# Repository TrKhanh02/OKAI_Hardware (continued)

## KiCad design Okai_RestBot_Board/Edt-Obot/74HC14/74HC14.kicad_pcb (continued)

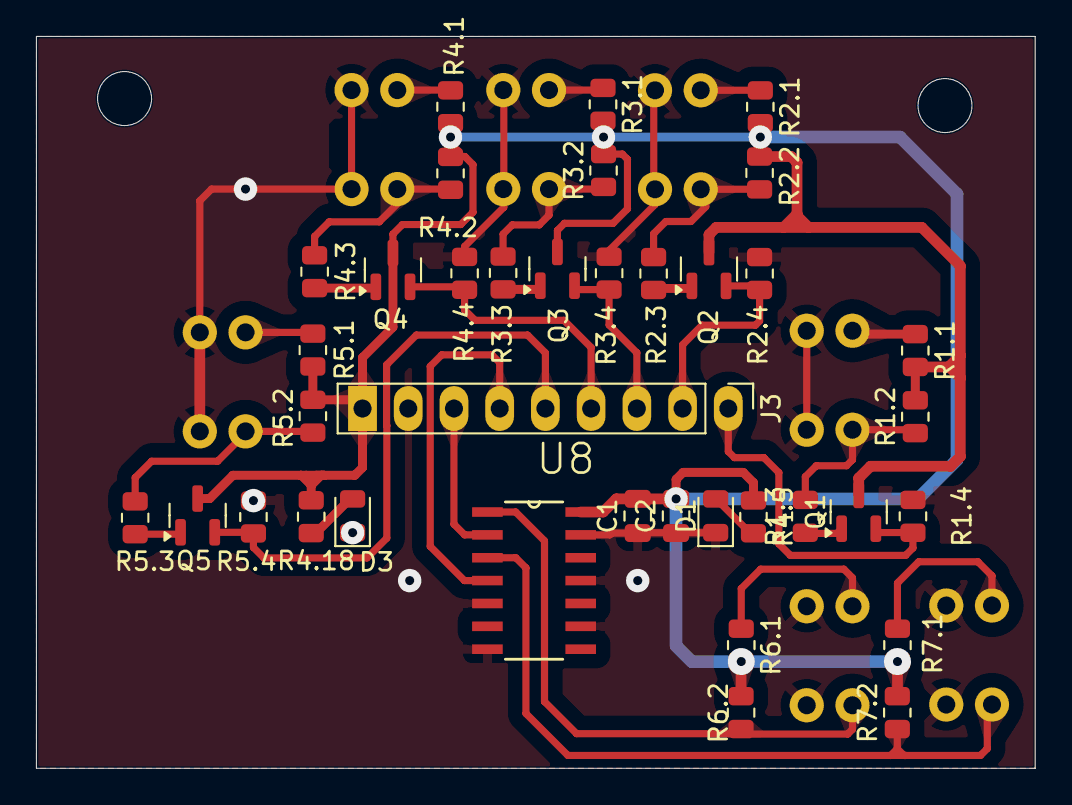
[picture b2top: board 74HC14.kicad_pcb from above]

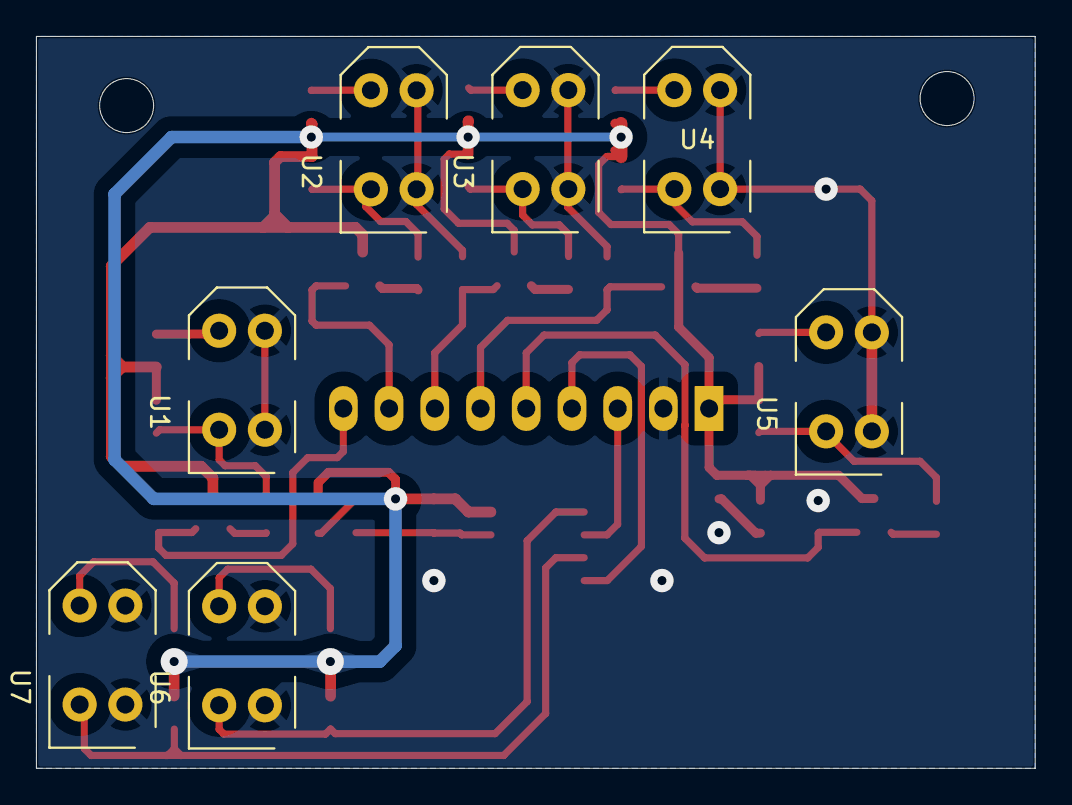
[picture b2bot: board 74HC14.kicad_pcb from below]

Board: 2 copper layers, 55.5 x 40.7 mm, 44 parts (7 on the bottom side), 30 nets.

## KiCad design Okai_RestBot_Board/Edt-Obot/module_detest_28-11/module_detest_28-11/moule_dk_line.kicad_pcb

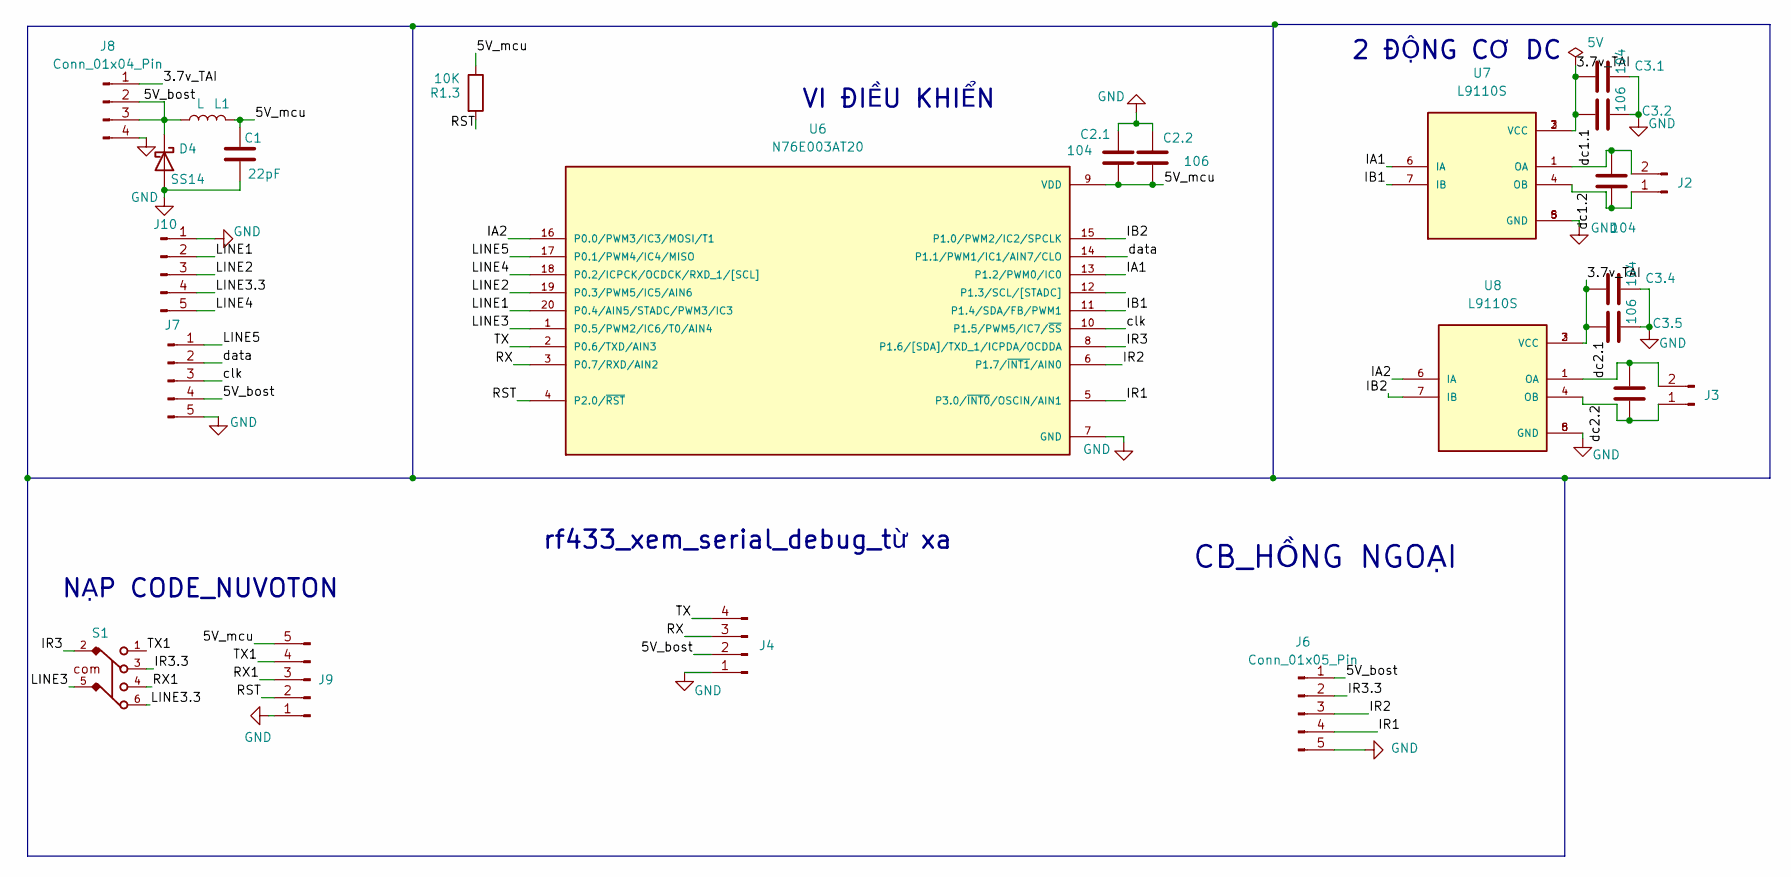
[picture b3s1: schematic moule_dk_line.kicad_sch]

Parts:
C1: 22pF; C_1206_3216Metric
C2.1, C3.1, C3.3, C3.4, C3.6: 104; C_0805_2012Metric
C2.2, C3.2, C3.5: 106; C_0805_2012Metric
D4: SS14; D_SMA
J2, J3: Conn_01x02_Pin; PinHeader_1x02_P2.54mm_Vertical
J4, J8: Conn_01x04_Pin; PinHeader_1x04_P2.54mm_Vertical
J6, J7, J9, J10: Conn_01x05_Pin; PinHeader_1x05_P2.54mm_Vertical
L1: L; L_6.3x6.3_H3
R1.3: 10K; R_0805_2012Metric
S1: 452406020024
U6: N76E003AT20; SOP65P640X120-20N; PARTREV 1.04
U7, U8: L9110S; SOIC127P599X172-8N; PARTREV NA

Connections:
/3.7v_TAI: C3.1.1, C3.2.1, C3.4.1, C3.5.1, J8.1, U7.2 (VCC), U7.3 (VCC), U8.2 (VCC), U8.3 (VCC)
/5V_bost: D4.1 (K), J4.2, J6.1, J7.4, J8.2, J8.3, L1.1
/5V_mcu: C1.1, C2.1.1, C2.2.1, J9.5, L1.2, R1.3.1, U6.9 (VDD)
/IA1: U6.13 (P1.2/PWM0/IC0), U7.6 (IA)
/IA2: U6.16 (P0.0/PWM3/IC3/MOSI/T1), U8.6 (IA)
/IB1: U6.11 (P1.4/SDA/FB/PWM1), U7.7 (IB)
/IB2: U6.15 (P1.0/PWM2/IC2/SPCLK), U8.7 (IB)
/IR1: J6.4, U6.5 (P3.0/~INT0/OSCIN/AIN1)
/IR2: J6.3, U6.6 (P1.7/~INT1/AIN0)
/IR3: S1.2, U6.8 (P1.6/[SDA]/TXD_1/ICPDA/OCDDA)
/IR3.3: J6.2, S1.3
/LINE1: J10.2, U6.20 (P0.4/AIN5/STADC/PWM3/IC3)
/LINE2: J10.3, U6.19 (P0.3/PWM5/IC5/AIN6)
/LINE3: S1.5, U6.1 (P0.5/PWM2/IC6/T0/AIN4)
/LINE3.3: J10.4, S1.6
/LINE4: J10.5, U6.18 (P0.2/ICPCK/OCDCK/RXD_1/[SCL])
/LINE5: J7.1, U6.17 (P0.1/PWM4/IC4/MISO)
/RST: J9.2, R1.3.2, U6.4 (P2.0/~RST)
/RX: J4.3, U6.3 (P0.7/RXD/AIN2)
/RX1: J9.3, S1.4
/TX: J4.4, U6.2 (P0.6/TXD/AIN3)
/TX1: J9.4, S1.1
/clk: J7.3, U6.10 (P1.5/PWM5/IC7/~SS)
/data: J7.2, U6.14 (P1.1/PWM1/IC1/AIN7/CLO)
/dc1.1: C3.3.1, J2.2, U7.1 (OA)
/dc1.2: C3.3.2, J2.1, U7.4 (OB)
/dc2.1: C3.6.1, J3.2, U8.1 (OA)
/dc2.2: C3.6.2, J3.1, U8.4 (OB)
GND: C1.2, C2.1.2, C2.2.2, C3.1.2, C3.2.2, C3.4.2, C3.5.2, D4.2 (A), J4.1, J6.5, J7.5, J8.4, J9.1, J10.1, U6.7 (GND), U7.5 (GND), U7.8 (GND), U8.5 (GND), U8.8 (GND)

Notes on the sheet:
VI ĐIỀU KHIỂN
CB_HỒNG NGOẠI
NẠP CODE_NUVOTON
2 ĐỘNG CƠ DC
rf433_xem_serial_debug_từ xa

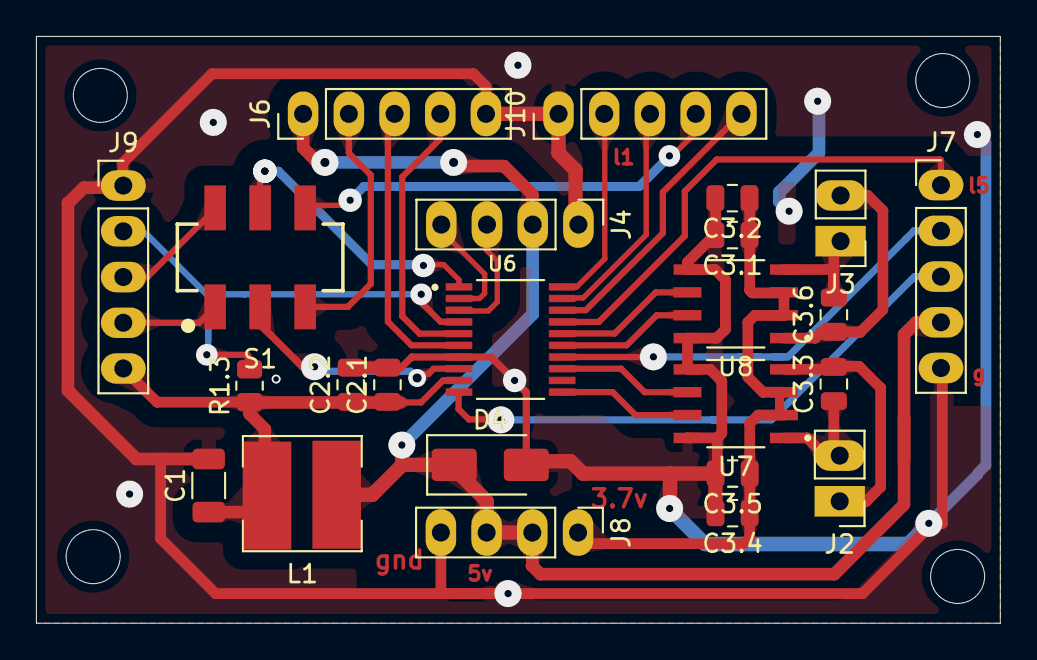
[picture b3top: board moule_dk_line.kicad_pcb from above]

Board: 2 copper layers, 53.5 x 32.6 mm, 24 parts (0 on the bottom side), 29 nets.

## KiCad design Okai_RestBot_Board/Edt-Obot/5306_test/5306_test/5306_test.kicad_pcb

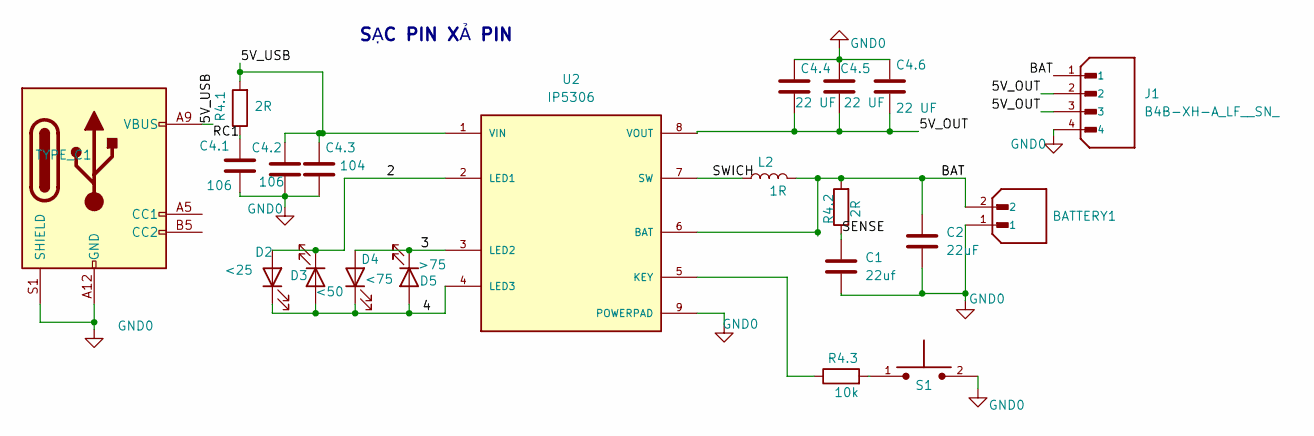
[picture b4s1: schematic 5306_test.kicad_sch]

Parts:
BATTERY1: B2B-XH-A_LF__SN_; JST_B2B-XH-A_LF__SN_; PARTREV N/A
C1: 22uf; C_1206_3216Metric_Pad1.33x1.80mm_HandSolder
C2: 22uF; C_1206_3216Metric_Pad1.33x1.80mm_HandSolder
C4.1, C4.2: 106; C_1206_3216Metric_Pad1.33x1.80mm_HandSolder
C4.3: 104; C_0805_2012Metric
C4.4, C4.5, C4.6: 22 UF; C_1206_3216Metric_Pad1.33x1.80mm_HandSolder
D2: <25; LED_0805_2012Metric_Pad1.15x1.40mm_HandSolder
D3: <50; LED_0805_2012Metric_Pad1.15x1.40mm_HandSolder
D4: <75; LED_0805_2012Metric_Pad1.15x1.40mm_HandSolder
D5: >75; LED_0805_2012Metric_Pad1.15x1.40mm_HandSolder
J1: B4B-XH-A_LF__SN_; JST_B4B-XH-A_LF__SN_; PARTREV 7/4/21
L2: 1R; L_7.3x7.3_H4.5
R4.1, R4.2: 2R; R_0805_2012Metric
R4.3: 10k; R_0805_2012Metric_Pad1.20x1.40mm_HandSolder
S1: TS10-63-26-BE-250-SMT-TR; SW_TS10-63-26-BE-250-SMT-TR; PARTREV 1.0
TYPE_C1: USB_C_Receptacle_PowerOnly_6P; USB_C_Receptacle_GCT_USB4125-xx-x_6P_TopMnt_Horizontal
U2: IP5306; SOP127P600X165-9N; PARTREV 1.31

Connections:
/2: D2.2 (A), D3.1 (K), U2.2 (LED1)
/3: D4.2 (A), D5.1 (K), U2.3 (LED2)
/4: D2.1 (K), D3.2 (A), D4.1 (K), D5.2 (A), U2.4 (LED3)
/5V_OUT: C4.4.2, C4.5.2, C4.6.2, J1.2, J1.3, U2.8 (VOUT)
/5V_USB: C4.2.1, C4.3.1, R4.1.2, TYPE_C1.A9 (VBUS), TYPE_C1.B9 (VBUS), U2.1 (VIN)
/BAT: BATTERY1.2, C2.1, J1.1, L2.2, R4.2.2, U2.6 (BAT)
/RC1: C4.1.1, R4.1.1
/SENSE: C1.1, R4.2.1
/SWICH: L2.1, U2.7 (SW)
GND0: BATTERY1.1, C1.2, C2.2, C4.1.2, C4.2.2, C4.3.2, C4.4.1, C4.5.1, C4.6.1, J1.4, S1.2, TYPE_C1.A12 (GND), TYPE_C1.B12 (GND), TYPE_C1.S1 (SHIELD), U2.9 (POWERPAD)
unnamed: R4.3.2, S1.1
unnamed: R4.3.1, U2.5 (KEY)

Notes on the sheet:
SẠC PIN XẢ PIN

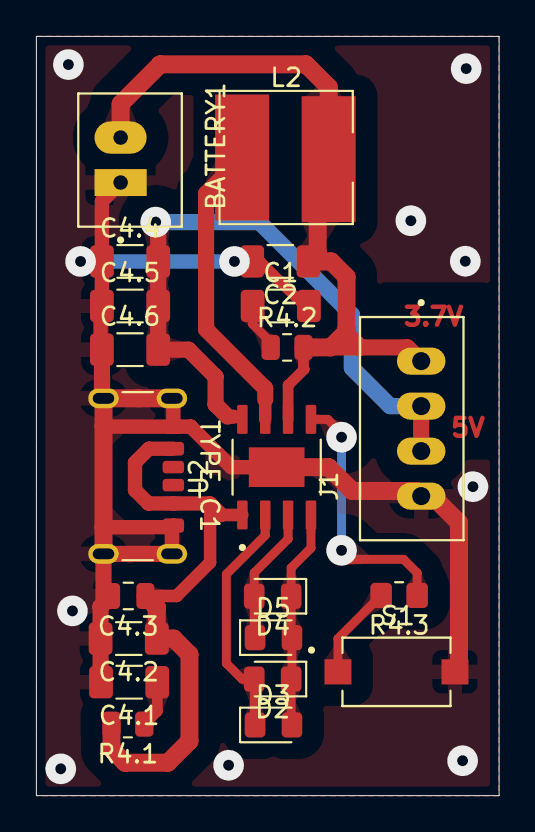
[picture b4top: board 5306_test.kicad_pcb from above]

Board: 2 copper layers, 25.7 x 42.2 mm, 21 parts (0 on the bottom side), 12 nets.

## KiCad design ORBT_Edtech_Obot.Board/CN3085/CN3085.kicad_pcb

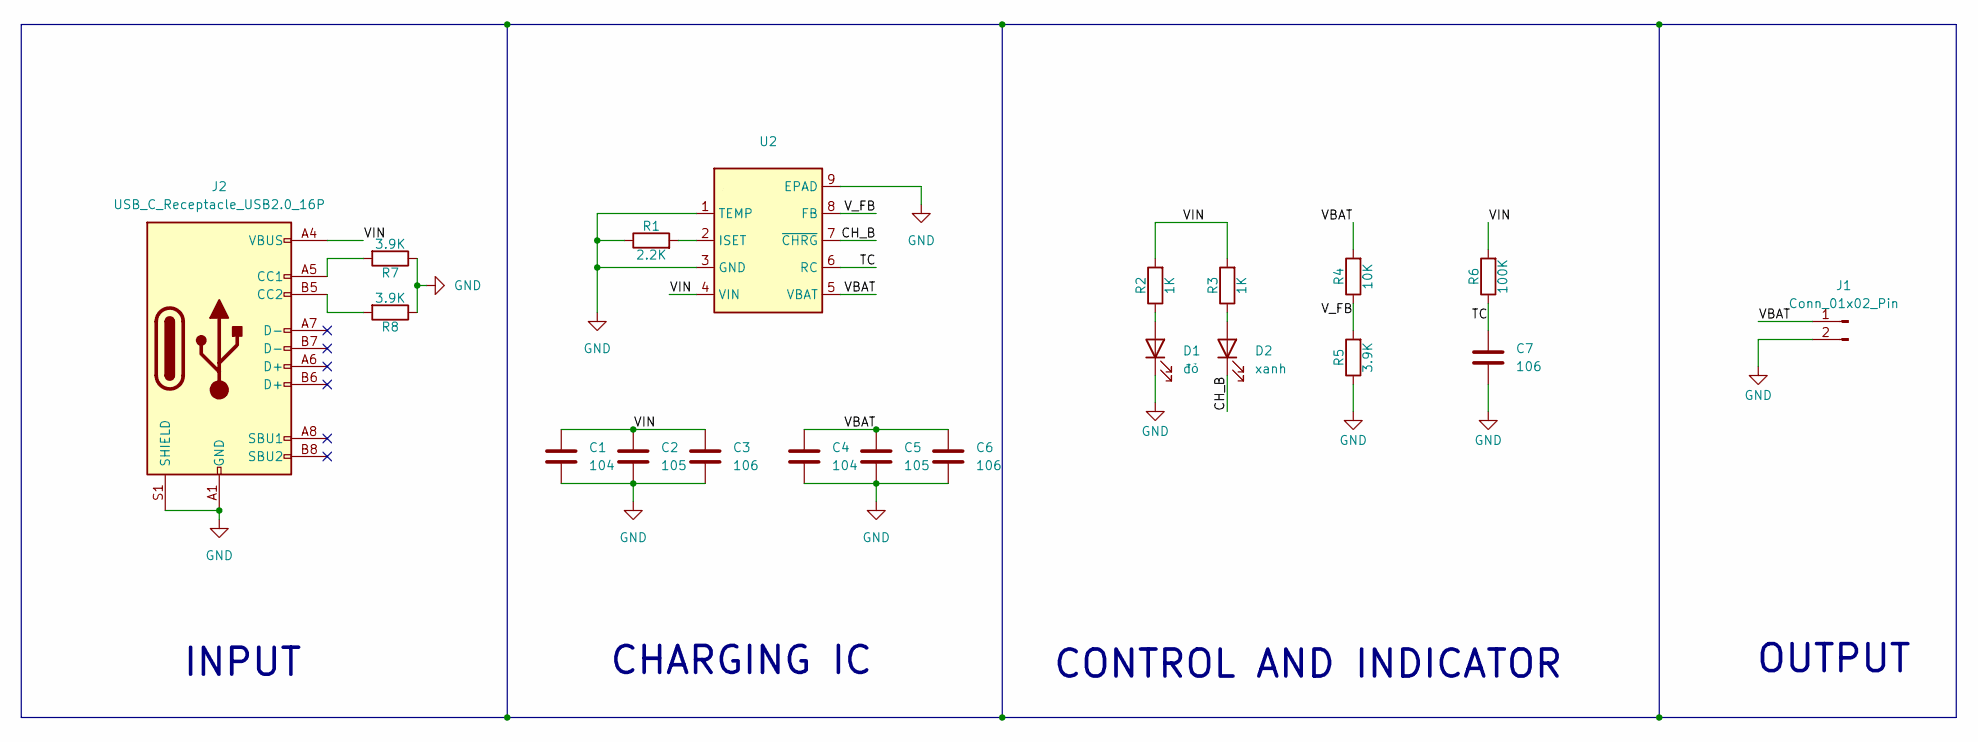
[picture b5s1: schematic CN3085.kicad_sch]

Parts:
C1, C4: 104; C_0805_2012Metric
C2, C5: 105; C_0805_2012Metric
C3, C6, C7: 106; C_0805_2012Metric
D1: đỏ; LED_0805_2012Metric_Pad1.15x1.40mm_HandSolder
D2: xanh; LED_0805_2012Metric_Pad1.15x1.40mm_HandSolder
J1: Conn_01x02_Pin; PinHeader_1x02_P2.54mm_Vertical
J2: USB_C_Receptacle_USB2.0_16P; USB_C_Receptacle_GCT_USB4105-xx-A_16P_TopMnt_Horizontal
R1: 2.2K; R_0805_2012Metric_Pad1.20x1.40mm_HandSolder
R2, R3: 1K; R_0805_2012Metric_Pad1.20x1.40mm_HandSolder
R4: 10K; R_0805_2012Metric_Pad1.20x1.40mm_HandSolder
R5, R7, R8: 3.9K; R_0805_2012Metric_Pad1.20x1.40mm_HandSolder
R6: 100K; R_0805_2012Metric_Pad1.20x1.40mm_HandSolder
U2: CN3085

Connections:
/CH_B: D2.1 (K), U2.7 (~CHRG)
/TC: C7.2, R6.1, U2.6 (RC)
/VBAT: C4.2, C5.2, C6.2, J1.1, R4.2, U2.5 (VBAT)
/VIN: C1.2, C2.2, C3.2, J2.A4 (VBUS), J2.A9 (VBUS), J2.B4 (VBUS), J2.B9 (VBUS), R2.2, R3.2, R6.2, U2.4 (VIN)
/V_FB: R4.1, R5.2, U2.8 (FB)
GND: C1.1, C2.1, C3.1, C4.1, C5.1, C6.1, C7.1, D1.1 (K), J1.2, J2.A1 (GND), J2.A12 (GND), J2.B1 (GND), J2.B12 (GND), J2.S1 (SHIELD), R1.1, R5.1, R7.1, R8.1, U2.1 (TEMP), U2.3 (GND), U2.9 (EPAD)
unnamed: D1.2 (A), R2.1
unnamed: D2.2 (A), R3.1
unnamed: J2.A5 (CC1), R7.2
unnamed: J2.B5 (CC2), R8.2
unnamed: R1.2, U2.2 (ISET)

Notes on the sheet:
CHARGING IC
INPUT
OUTPUT
CONTROL AND INDICATOR

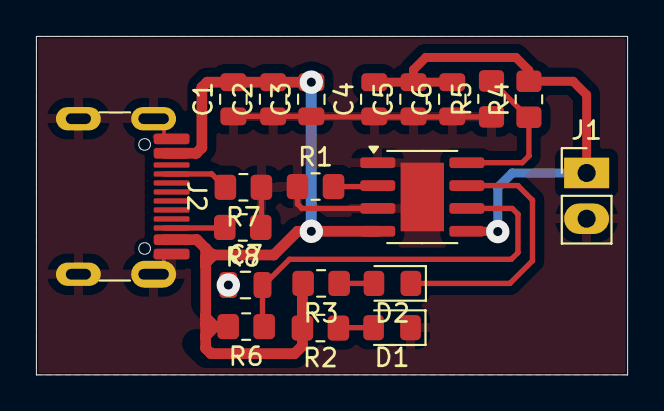
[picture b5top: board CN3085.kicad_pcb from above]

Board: 2 copper layers, 32.8 x 18.8 mm, 20 parts (0 on the bottom side), 11 nets.

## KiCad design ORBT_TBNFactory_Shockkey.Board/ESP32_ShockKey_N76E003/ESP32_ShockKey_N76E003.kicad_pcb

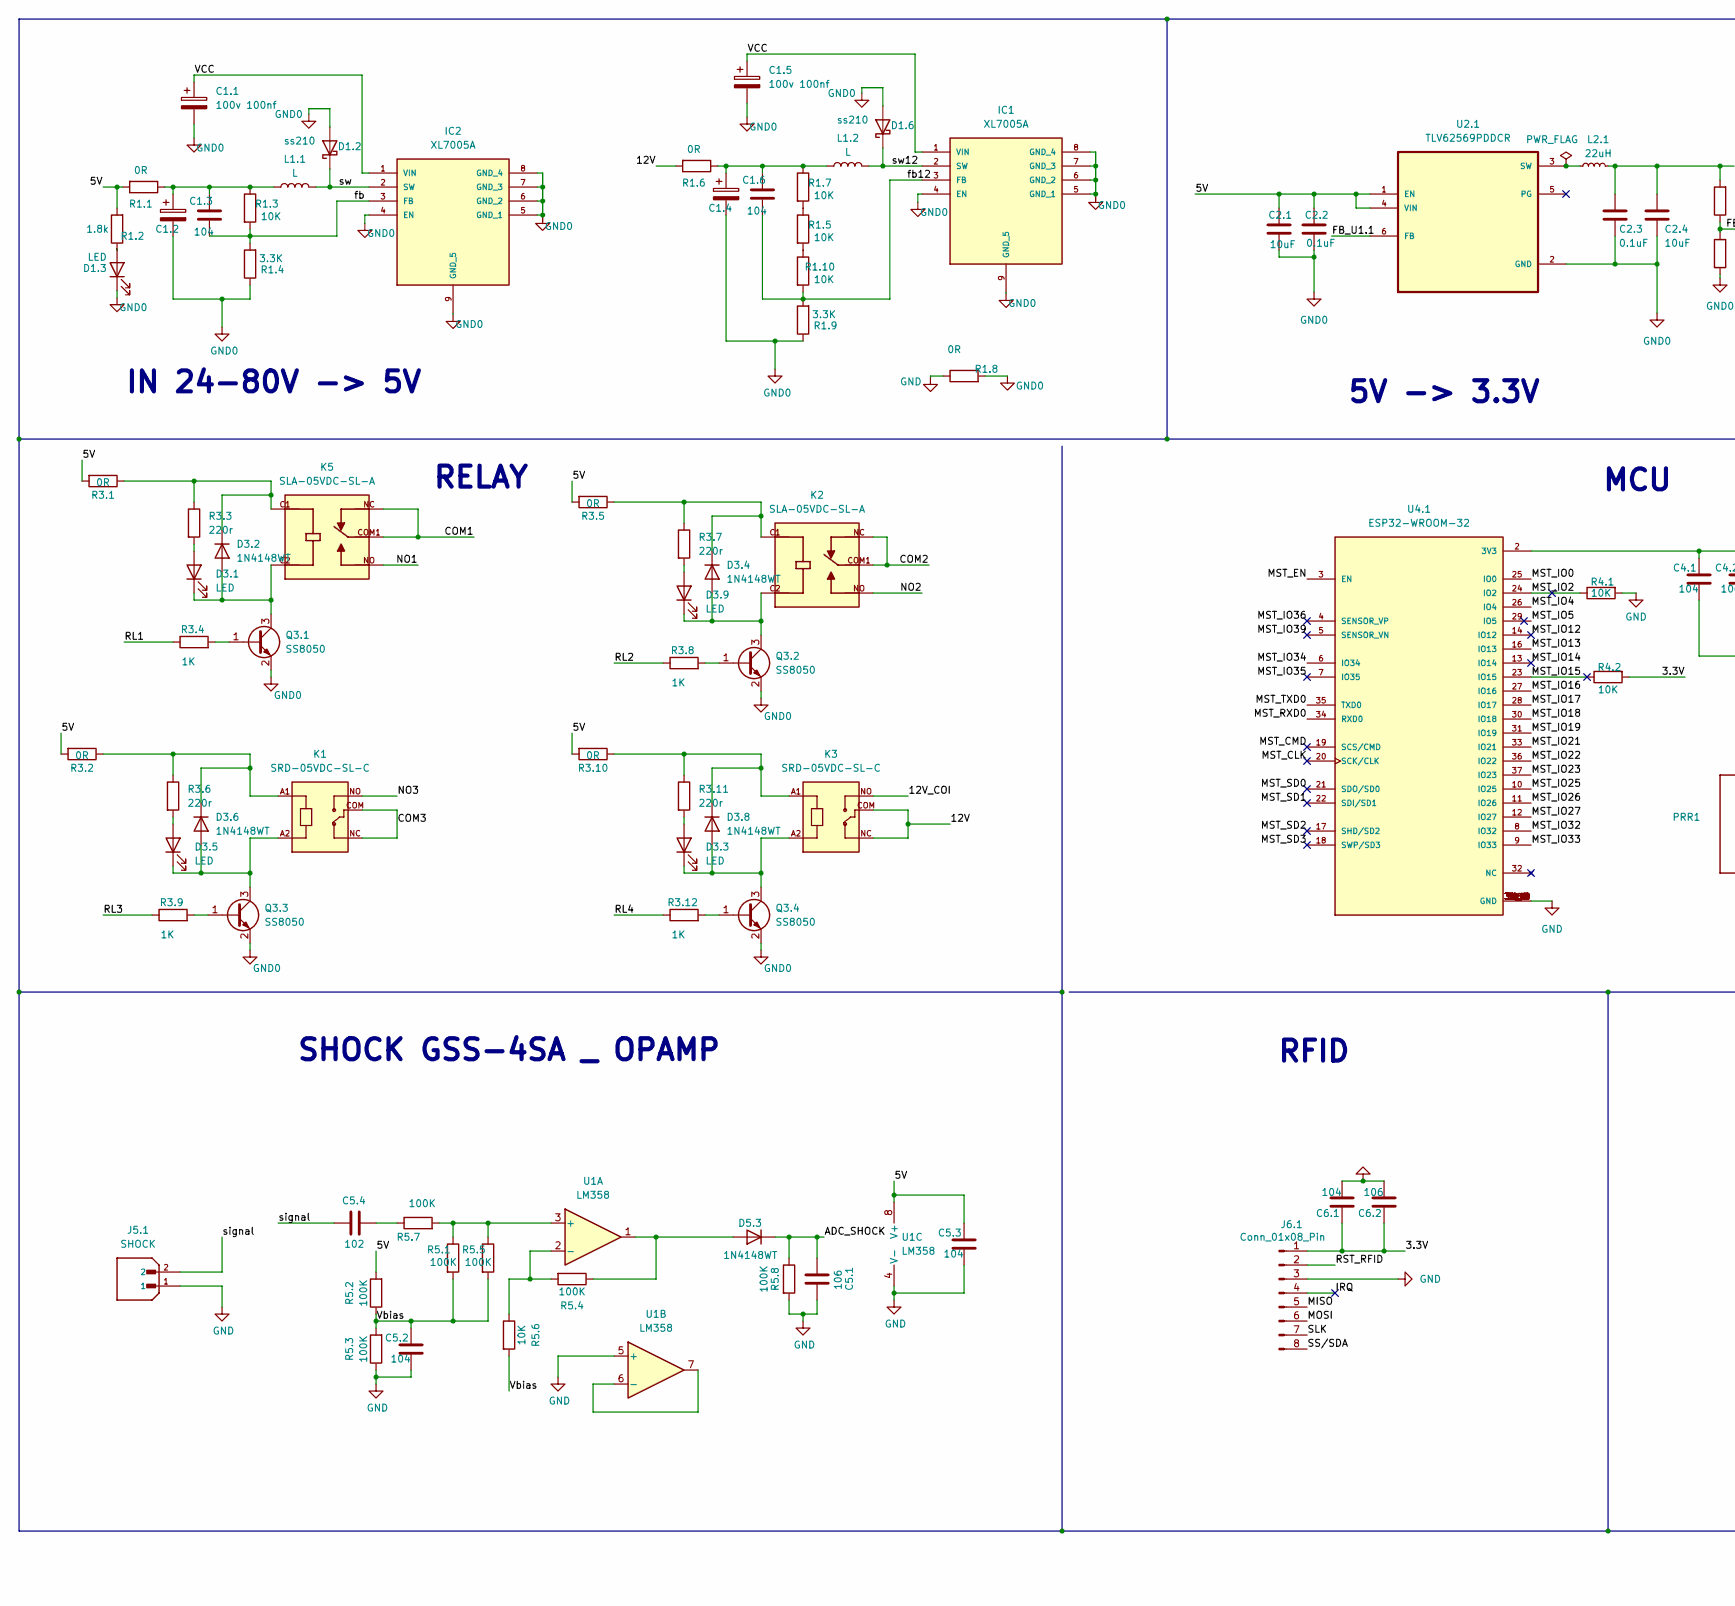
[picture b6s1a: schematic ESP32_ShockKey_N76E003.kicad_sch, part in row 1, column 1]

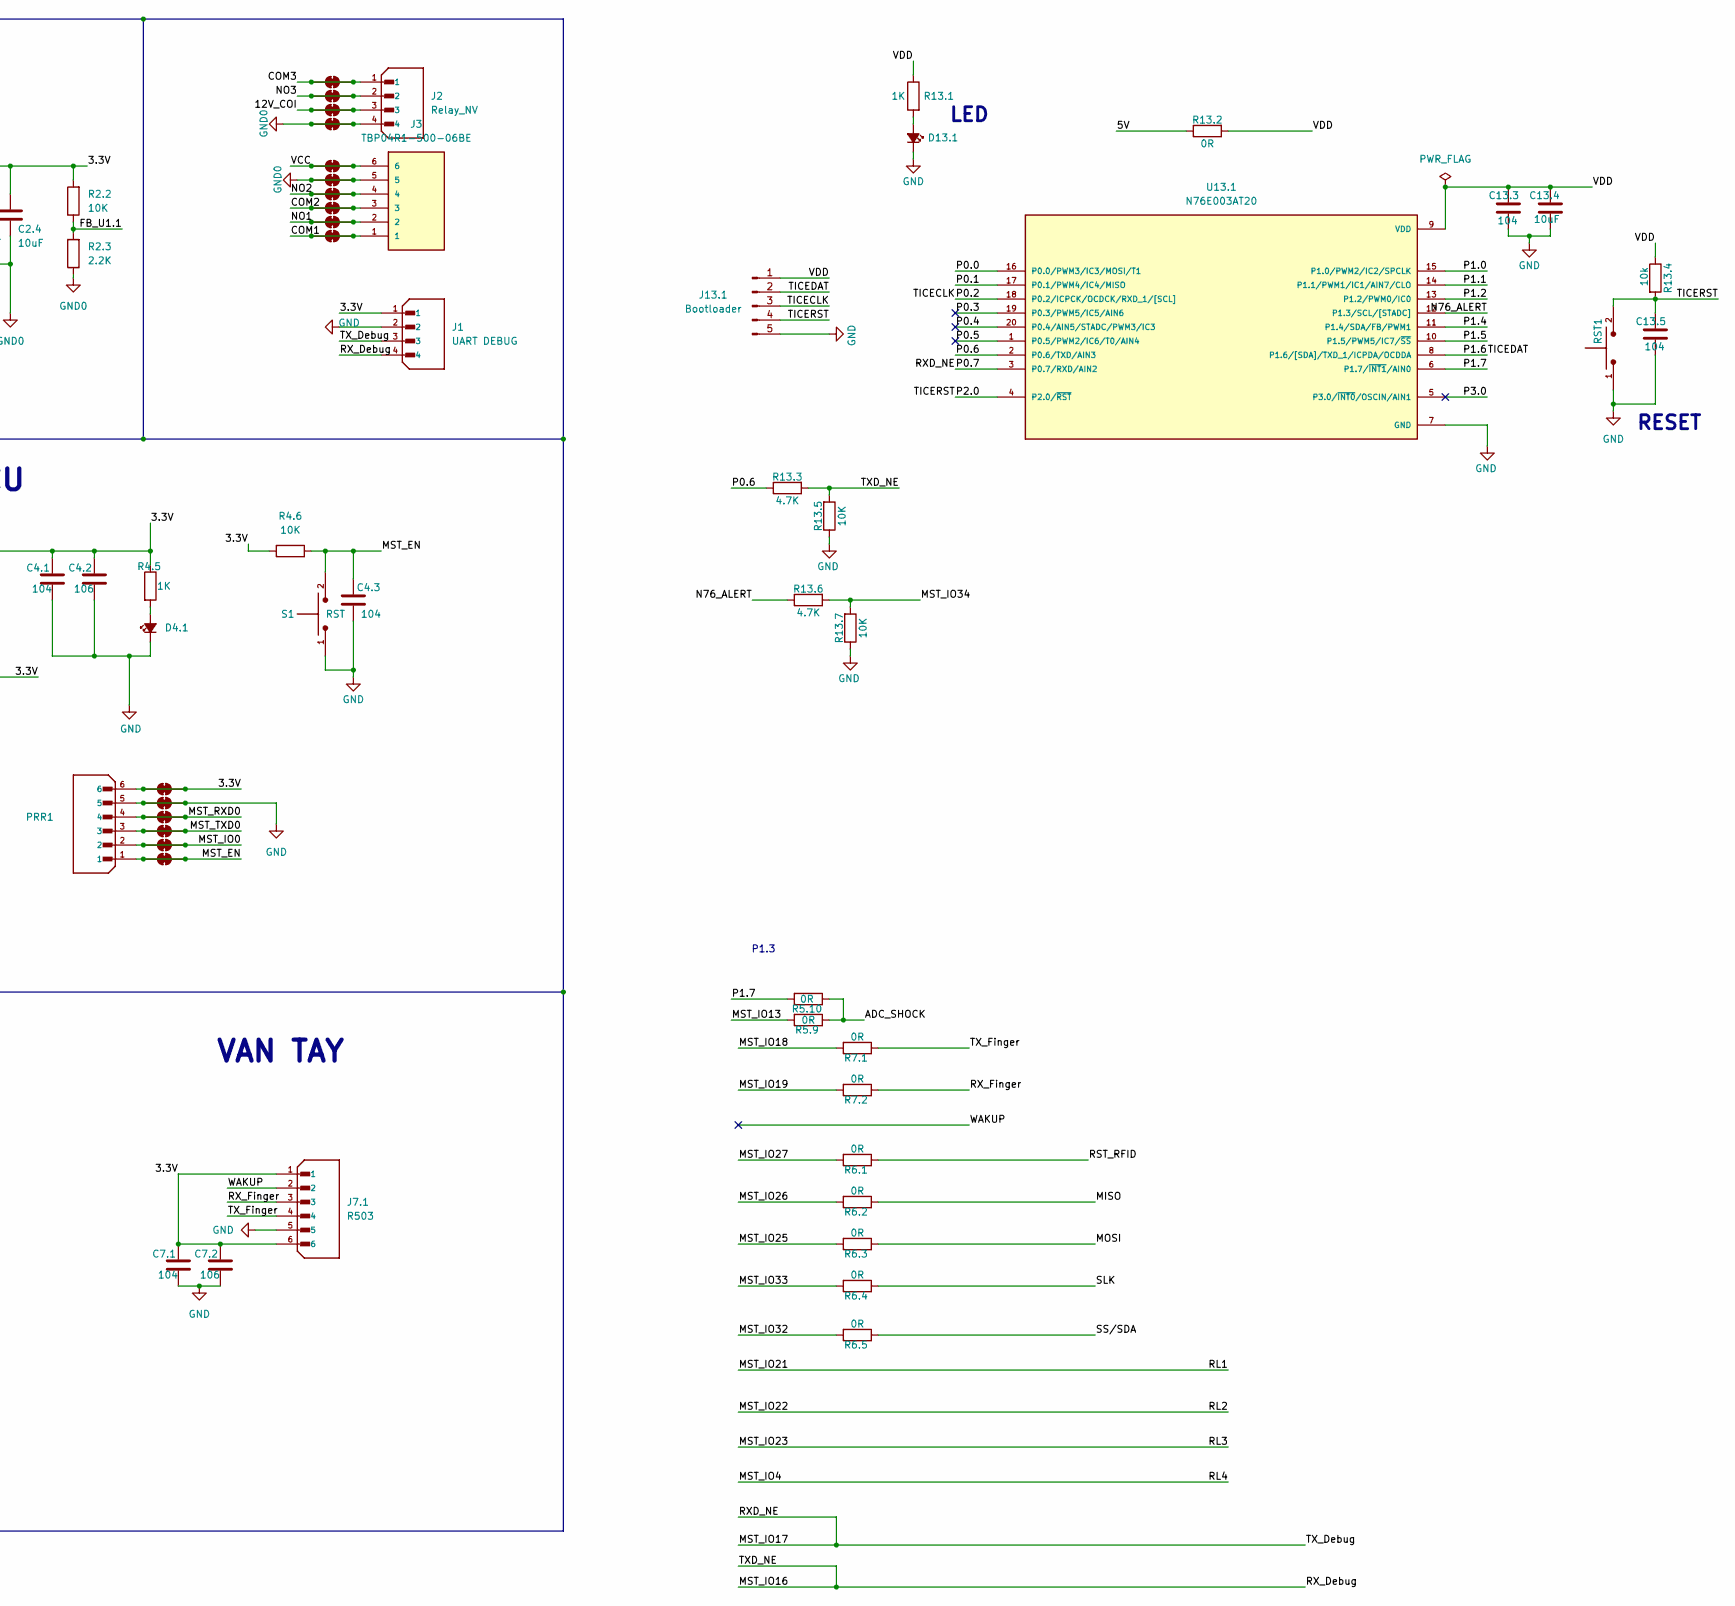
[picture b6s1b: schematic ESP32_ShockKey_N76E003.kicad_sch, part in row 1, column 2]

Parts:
C1.1, C1.5: 100v 100nf; CP_Radial_D6.3mm_P2.50mm
C1.2, C1.4: C_Polarized; CP_Elec_6.3x5.4
C1.3, C1.6, C4.3: 104; C_0805_2012Metric
C2.1, C2.4: 10uF; C_0805_2012Metric
C2.2, C2.3: 0.1uF; C_0805_2012Metric
C4.1, C5.2, C5.3, C6.1, C7.1, C13.3, C13.5: 104; C_0805_2012Metric_Pad1.18x1.45mm_HandSolder
C4.2, C5.1, C6.2, C7.2: 106; C_0805_2012Metric_Pad1.18x1.45mm_HandSolder
C5.4: 102; C_0805_2012Metric_Pad1.18x1.45mm_HandSolder
C13.4: 10uF; C_0805_2012Metric_Pad1.18x1.45mm_HandSolder
D1.2, D1.6: ss210; D_SMA
D1.3, D3.1, D3.3, D3.5, D3.9: LED; LED_0805_2012Metric
D3.2, D3.4, D3.6, D3.8, D5.3: 1N4148WT; D_SOD-523
D4.1, D13.1: LED_Small_Filled; LED_0805_2012Metric_Pad1.15x1.40mm_HandSolder
IC1, IC2: XL7005A; SOIC127P600X175-9N; Manufacturer_Part_Number XL7005A
J1: UART DEBUG; JST_B4B-XH-A_LF__SN_; PARTREV 7/4/21
J2: Relay_NV; JST_B4B-XH-A_LF__SN_; PARTREV 7/4/21
J3: TBP04R1-500-06BE; CUI_TBP04R1-500-06BE; PARTREV 1.0
J5.1: SHOCK; JST_B2B-XH-A_LF__SN_; PARTREV N/A
J6.1: Conn_01x08_Pin; PinHeader_1x08_P2.54mm_Vertical
J7.1: R503; JST_B6B-XH-A_LF__SN_; PARTREV 7/4/21
J13.1: Bootloader; PinHeader_1x05_P2.54mm_Vertical
JP1, JP2, JP3, JP4, JP5, JP6, JP7, JP8, JP9, JP10, JP11, JP12, JP13, JP14, JP15, JP16: SolderJumper_2_Bridged; SolderJumper-2_P1.3mm_Bridged_Pad1.0x1.5mm
K1, K3: SRD-05VDC-SL-C; RELAY_SRD-05VDC-SL-C
K2, K5: SLA-05VDC-SL-A; RELAY_SLA-12VDC-SL-C
L1.1, L1.2: L; L_10.4x10.4_H4.8
L2.1: 22uH; L_Ferrocore_DLG-0705
PRR1: B6B-XH-A_LF__SN_; JST_B6B-XH-A_LF__SN_; PARTREV 7/4/21
Q3.1, Q3.2, Q3.3, Q3.4: SS8050; SOT-23
R1.1, R1.6, R1.8, R5.9, R5.10, R6.1, R6.2, R6.3, R6.4, R6.5, R7.1, R7.2: 0R; R_0805_2012Metric
R1.2: 1.8k; R_0805_2012Metric
R1.3, R1.5, R1.7, R1.10, R2.2, R4.6, R5.6: 10K; R_0805_2012Metric
R1.4, R1.9: 3.3K; R_0805_2012Metric
R2.3: 2.2K; R_0805_2012Metric
R3.1, R3.2, R3.5, R3.10, R13.2: 0R; R_0805_2012Metric_Pad1.20x1.40mm_HandSolder
R3.3, R3.6, R3.7, R3.11: 220r; R_0805_2012Metric_Pad1.20x1.40mm_HandSolder
R3.4, R3.8, R3.9, R3.12, R4.5, R13.1: 1K; R_0805_2012Metric_Pad1.20x1.40mm_HandSolder
R4.1, R4.2, R13.5, R13.7: 10K; R_0805_2012Metric_Pad1.20x1.40mm_HandSolder
R5.1, R5.2, R5.3, R5.4, R5.5, R5.7, R5.8: 100K; R_0805_2012Metric
R13.3, R13.6: 4.7K; R_0805_2012Metric_Pad1.20x1.40mm_HandSolder
R13.4: 10k; R_0805_2012Metric_Pad1.20x1.40mm_HandSolder
RST1: TS10-63-26-BE-250-SMT-TR; SW_TS10-63-26-BE-250-SMT-TR; PARTREV 1.0
S1: RST; SW_TS10-63-26-BE-250-SMT-TR; PARTREV 1.0
U1: LM358; LFCSP-8_2x2mm_P0.5mm
U2.1: TLV62569PDDCR; SOT95P280X110-6N
U4.1: ESP32-WROOM-32; MODULE_ESP32-WROOM-32
U13.1: N76E003AT20; SOP65P640X120-20N; PARTREV 1.04

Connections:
/3.3V: C2.3.1, C2.4.1, C4.1.1, C4.2.1, C6.1.1, C6.2.1, C7.1.1, C7.2.1, J1.1, J6.1.1, J7.1.1, J7.1.6, JP13.1 (A), JP13.2 (B), L2.1.1, PRR1.6, R2.2.2, R4.2.2, R4.5.1, R4.6.1, U4.1.2 (3V3)
/5V: C2.1.1, C2.2.1, C5.3.1, R1.1.2, R1.2.2, R3.1.2, R3.2.2, R3.5.2, R3.10.2, R5.2.2, R13.2.1, U1.8 (V+), U2.1.1 (EN), U2.1.4 (VIN)
/12V: K3.COM, K3.NC, R1.6.2
/12V_COI: J2.3, JP3.1 (A), JP3.2 (B), K3.NO
/ADC_SHOCK: C5.1.2, D5.3.1 (K), R5.8.1, R5.9.1, R5.10.1
/COM1: J3.1, JP16.1 (A), JP16.2 (B), K5.COM1, K5.COM2, K5.NC
/COM2: J3.3, JP14.1 (A), JP14.2 (B), K2.COM1, K2.COM2, K2.NC
/COM3: J2.1, JP1.1 (A), JP1.2 (B), K1.COM, K1.NC
/FB_U1.1: R2.2.1, R2.3.2, U2.1.6 (FB)
/IRQ: J6.1.4
/MISO: J6.1.5, R6.2.1
/MOSI: J6.1.6, R6.3.1
/MST_CLK: U4.1.20 (SCK/CLK)
/MST_CMD: U4.1.19 (SCS/CMD)
/MST_EN: C4.3.1, JP8.1 (A), JP8.2 (B), PRR1.1, R4.6.2, S1.2, U4.1.3 (EN)
/MST_IO0: JP9.1 (A), JP9.2 (B), PRR1.2, U4.1.25 (IO0)
/MST_IO2: R4.1.1, U4.1.24 (IO2)
/MST_IO4: R3.12.1, U4.1.26 (IO4)
/MST_IO5: U4.1.29 (IO5)
/MST_IO12: U4.1.14 (IO12)
/MST_IO13: R5.9.2, U4.1.16 (IO13)
/MST_IO14: U4.1.13 (IO14)
/MST_IO15: R4.2.1, U4.1.23 (IO15)
/MST_IO16: J1.4, R13.3.2, R13.5.2, U4.1.27 (IO16)
/MST_IO17: J1.3, U4.1.28 (IO17), U13.1.3 (P0.7/RXD/AIN2)
/MST_IO18: R7.1.2, U4.1.30 (IO18)
/MST_IO19: R7.2.2, U4.1.31 (IO19)
/MST_IO21: R3.4.1, U4.1.33 (IO21)
/MST_IO22: R3.8.1, U4.1.36 (IO22)
/MST_IO23: R3.9.1, U4.1.37 (IO23)
/MST_IO25: R6.3.2, U4.1.10 (IO25)
/MST_IO26: R6.2.2, U4.1.11 (IO26)
/MST_IO27: R6.1.2, U4.1.12 (IO27)
/MST_IO32: R6.5.2, U4.1.8 (IO32)
/MST_IO33: R6.4.2, U4.1.9 (IO33)
/MST_IO34: R13.6.2, R13.7.2, U4.1.6 (IO34)
/MST_IO35: U4.1.7 (IO35)
/MST_IO36: U4.1.4 (SENSOR_VP)
/MST_IO39: U4.1.5 (SENSOR_VN)
/MST_RXD0: JP11.1 (A), JP11.2 (B), PRR1.4, U4.1.34 (RXD0)
/MST_SD0: U4.1.21 (SDO/SD0)
/MST_SD1: U4.1.22 (SDI/SD1)
/MST_SD2: U4.1.17 (SHD/SD2)
/MST_SD3: U4.1.18 (SWP/SD3)
/MST_TXD0: JP10.1 (A), JP10.2 (B), PRR1.3, U4.1.35 (TXD0)
/N76_ALERT: R13.6.1, U13.1.12 (P1.3/SCL/[STADC])
/NO1: J3.2, JP15.1 (A), JP15.2 (B), K5.NO
/NO2: J3.4, JP7.1 (A), JP7.2 (B), K2.NO
/NO3: J2.2, JP2.1 (A), JP2.2 (B), K1.NO
/P0.0: U13.1.16 (P0.0/PWM3/IC3/MOSI/T1)
/P0.1: U13.1.17 (P0.1/PWM4/IC4/MISO)
/P0.2: J13.1.3, U13.1.18 (P0.2/ICPCK/OCDCK/RXD_1/[SCL])
/P0.3: U13.1.19 (P0.3/PWM5/IC5/AIN6)
/P0.4: U13.1.20 (P0.4/AIN5/STADC/PWM3/IC3)
/P0.5: U13.1.1 (P0.5/PWM2/IC6/T0/AIN4)
/P0.6: R13.3.1, U13.1.2 (P0.6/TXD/AIN3)
/P1.0: U13.1.15 (P1.0/PWM2/IC2/SPCLK)
/P1.1: U13.1.14 (P1.1/PWM1/IC1/AIN7/CLO)
/P1.2: U13.1.13 (P1.2/PWM0/IC0)
/P1.4: U13.1.11 (P1.4/SDA/FB/PWM1)
/P1.5: U13.1.10 (P1.5/PWM5/IC7/~SS)
/P1.6: J13.1.2, U13.1.8 (P1.6/[SDA]/TXD_1/ICPDA/OCDDA)
/P1.7: R5.10.2, U13.1.6 (P1.7/~INT1/AIN0)
/P2.0: C13.5.1, J13.1.4, R13.4.2, RST1.2, U13.1.4 (P2.0/~RST)
/P3.0: U13.1.5 (P3.0/~INT0/OSCIN/AIN1)
/RST_RFID: J6.1.2, R6.1.1
/RX_Finger: J7.1.3, R7.2.1
/SLK: J6.1.7, R6.4.1
/SS/SDA: J6.1.8, R6.5.1
/TX_Finger: J7.1.4, R7.1.1
/VCC: C1.1.1, C1.5.1, IC1.1 (VIN), IC2.1 (VIN), J3.6, JP5.1 (A), JP5.2 (B)
/VDD: C13.3.1, C13.4.1, J13.1.1, R13.1.1, R13.2.2, R13.4.1, U13.1.9 (VDD)
/Vbias: C5.2.1, R5.1.2, R5.2.1, R5.3.2, R5.5.2, R5.6.2
/WAKUP: J7.1.2
/fb: C1.3.2, IC2.3 (FB), R1.3.2, R1.4.2
/fb12: C1.6.2, IC1.3 (FB), R1.9.2, R1.10.2
/signal: C5.4.1, J5.1.2
/sw: D1.2.1 (K), IC2.2 (SW), L1.1.2
/sw12: D1.6.1 (K), IC1.2 (SW), L1.2.2
GND: C4.1.2, C4.2.2, C4.3.2, C5.1.1, C5.2.2, C5.3.2, C6.1.2, C6.2.2, C7.1.2, C7.2.2, C13.3.2, C13.4.2, C13.5.2, D4.1.1 (K), D13.1.1 (K), J1.2, J5.1.1, J6.1.3, J7.1.5, J13.1.5, JP12.1 (A), JP12.2 (B), PRR1.5, R1.8.1, R4.1.2, R5.3.1, R5.8.2, R13.5.1, R13.7.1, RST1.1, S1.1, U1.4 (V-), U1.5 (+), U4.1.1 (GND), U4.1.15 (GND), U4.1.38 (GND), U4.1.39_1 (GND), U4.1.39_2 (GND), U4.1.39_3 (GND), U4.1.39_4 (GND), U4.1.39_5 (GND), U4.1.39_6 (GND), U4.1.39_7 (GND), U4.1.39_8 (GND), U4.1.39_9 (GND), U4.1.39_10 (GND), U4.1.39_11 (GND), U4.1.39_12 (GND), U4.1.39_13 (GND), U4.1.39_14 (GND), U4.1.39_15 (GND), U4.1.39_16 (GND), U4.1.39_17 (GND), U4.1.39_18 (GND), U4.1.39_19 (GND), U4.1.39_20 (GND), U4.1.39_21 (GND), U13.1.7 (GND)
GND0: C1.1.2, C1.2.2, C1.4.2, C1.5.2, C2.1.2, C2.2.2, C2.3.2, C2.4.2, D1.2.2 (A), D1.3.1 (K), D1.6.2 (A), IC1.4 (EN), IC1.5 (GND_1), IC1.6 (GND_2), IC1.7 (GND_3), IC1.8 (GND_4), IC1.9 (GND_5), IC2.4 (EN), IC2.5 (GND_1), IC2.6 (GND_2), IC2.7 (GND_3), IC2.8 (GND_4), IC2.9 (GND_5), J2.4, J3.5, JP4.1 (A), JP4.2 (B), JP6.1 (A), JP6.2 (B), Q3.1.2 (E), Q3.2.2 (E), Q3.3.2 (E), Q3.4.2 (E), R1.4.1, R1.8.2, R1.9.1, R2.3.1, U2.1.2 (GND)
unnamed: C1.2.1, C1.3.1, L1.1.1, R1.1.1, R1.3.1
unnamed: C1.4.1, C1.6.1, L1.2.1, R1.6.1, R1.7.1
unnamed: C5.4.2, R5.7.1
unnamed: D1.3.2 (A), R1.2.1
unnamed: D3.1.2 (A), R3.3.2
unnamed: D3.1.1 (K), D3.2.2 (A), K5.C2, Q3.1.3 (C)
unnamed: D3.2.1 (K), K5.C1, R3.1.1, R3.3.1
unnamed: D3.3.2 (A), R3.11.2
unnamed: D3.3.1 (K), D3.8.2 (A), K3.A2, Q3.4.3 (C)
unnamed: D3.4.2 (A), D3.9.1 (K), K2.C2, Q3.2.3 (C)
unnamed: D3.4.1 (K), K2.C1, R3.5.1, R3.7.1
unnamed: D3.5.2 (A), R3.6.2
unnamed: D3.5.1 (K), D3.6.2 (A), K1.A2, Q3.3.3 (C)
unnamed: D3.6.1 (K), K1.A1, R3.2.1, R3.6.1
unnamed: D3.8.1 (K), K3.A1, R3.10.1, R3.11.1
unnamed: D3.9.2 (A), R3.7.2
unnamed: D4.1.2 (A), R4.5.2
unnamed: D5.3.2 (A), R5.4.1, U1.1
unnamed: D13.1.2 (A), R13.1.2
unnamed: Q3.1.1 (B), R3.4.2
unnamed: Q3.2.1 (B), R3.8.2
unnamed: Q3.3.1 (B), R3.9.2
unnamed: Q3.4.1 (B), R3.12.2
unnamed: R1.5.1, R1.7.2
unnamed: R1.5.2, R1.10.1
unnamed: R5.1.1, R5.5.1, R5.7.2, U1.3 (+)
unnamed: R5.4.2, R5.6.1, U1.2 (-)
unnamed: U1.6 (-), U1.7
unnamed: L2.1.2, U2.1.3 (SW)

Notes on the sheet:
P1.3
MCU
VAN TAY
RELAY
RFID
IN 24-80V -> 5V
RESET
SHOCK GSS-4SA _ OPAMP
5V -> 3.3V
LED

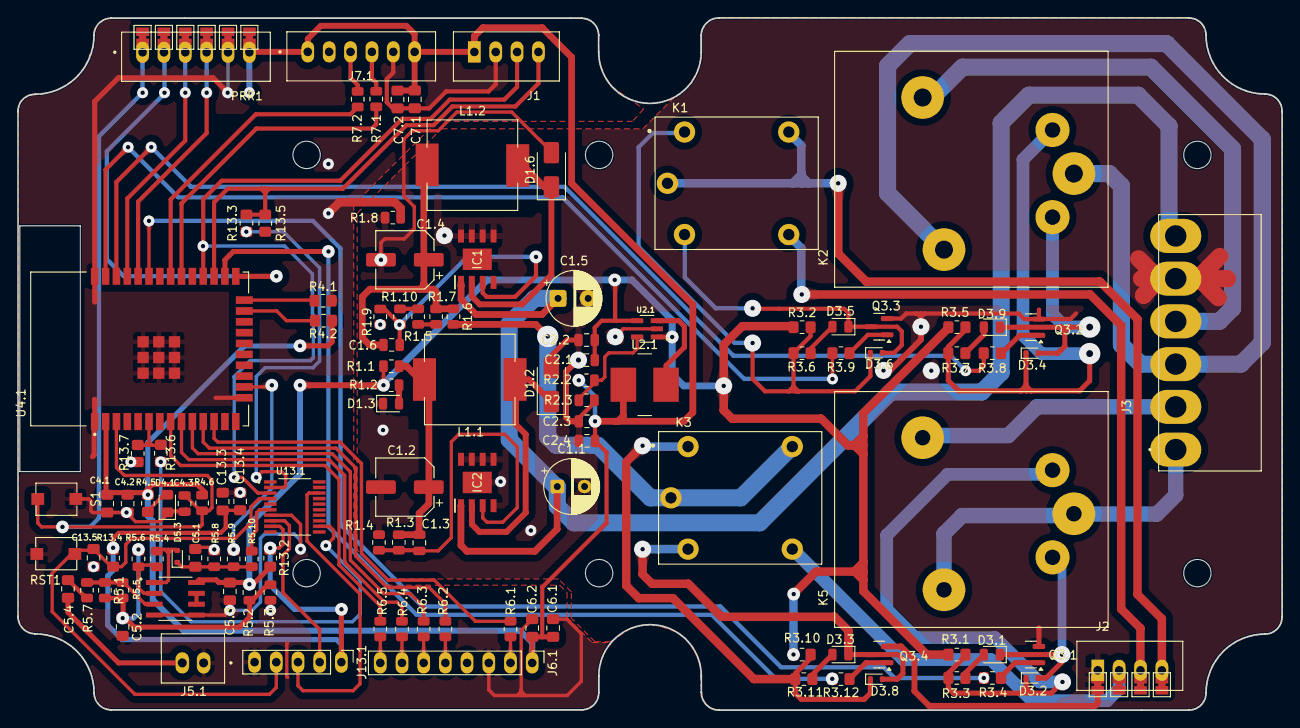
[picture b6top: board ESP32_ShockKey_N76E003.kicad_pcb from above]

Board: 2 copper layers, 147.9 x 81.0 mm, 125 parts (0 on the bottom side), 84 nets.
